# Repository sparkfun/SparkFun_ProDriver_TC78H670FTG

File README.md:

SparkFun ProDriver - Stepper Motor Driver (TC78H670FTG)
========================================

[*SparkFun ProDriver - Stepper Motor Driver (TC78H670FTG) (ROB-16836)*](https://www.sparkfun.com/products/16836)

The SparkFun ProDriver makes it easy to start developing with the TC78H670FTG bipolar stepper motor driver from Toshiba! Latch terminals provide instant solder-less connections to every feature offered. Use our extensive Arduino Library with 10 examples, and you can quickly explore the many features of this precise and small package size motor driver IC.

In addition to high resolution control (down to 1/128th of a step), the ProDriver can be controlled via traditional clock-in stepping or serial commands. Both methods are demonstrated in the Arduino Library. The serial command method is especially unique in that it allows the user to precisely control the phase, torque, current limit and mixed decay ratio of each coil immediately during stepping. Most stepper motor driver ICs require using an external trimpot to set the current limit, but with the ProDriver, you can precisely adjust this via serial commands!

Repository Contents
-------------------

* **/Documentation** - Datasheets, additional product information
* **/Hardware** - Eagle design files (.brd, .sch)
* **/Hardware/Production** - Production panel files and gerbers (.brd)

Documentation
--------------

* **[Hookup Guide](https://learn.sparkfun.com/tutorials/1200)** - A hookup guide for the SparkFun ProDriver and Mini Stepper Motor Driver (TC78H670FTG)
* **[Arduino Library](https://github.com/sparkfun/SparkFun_ProDriver_TC78H670FTG_Arduino_Library)** - Basic Arduino Library for the SparkFun ProDriver and Mini Stepper Motor Driver (TC78H670FTG)

Product Variants
----------------
* SparkFun Mini Stepper Motor Driver - TC78H670FTG
  * [ROB-25167](https://www.sparkfun.com/products/25167)- v1.0, Initial Release
* SparkFun ProDriver - Stepper Motor Driver (TC78H670FTG)
  * [ROB-16836](https://www.sparkfun.com/products/16836)- v1.0, Initial Release

Product Versions
----------------
* [v01](https://github.com/sparkfun/SparkFun_ProDriver_TC78H670FTG/releases/tag/v10) - Initial Release

License Information
-------------------

This product is _**open source**_!

Please review the LICENSE.md file for license information.

If you have any questions or concerns on licensing, please contact technical support on our [SparkFun forums](https://forum.sparkfun.com/viewforum.php?f=152).

Distributed as-is; no warranty is given.

- Your friends at SparkFun.

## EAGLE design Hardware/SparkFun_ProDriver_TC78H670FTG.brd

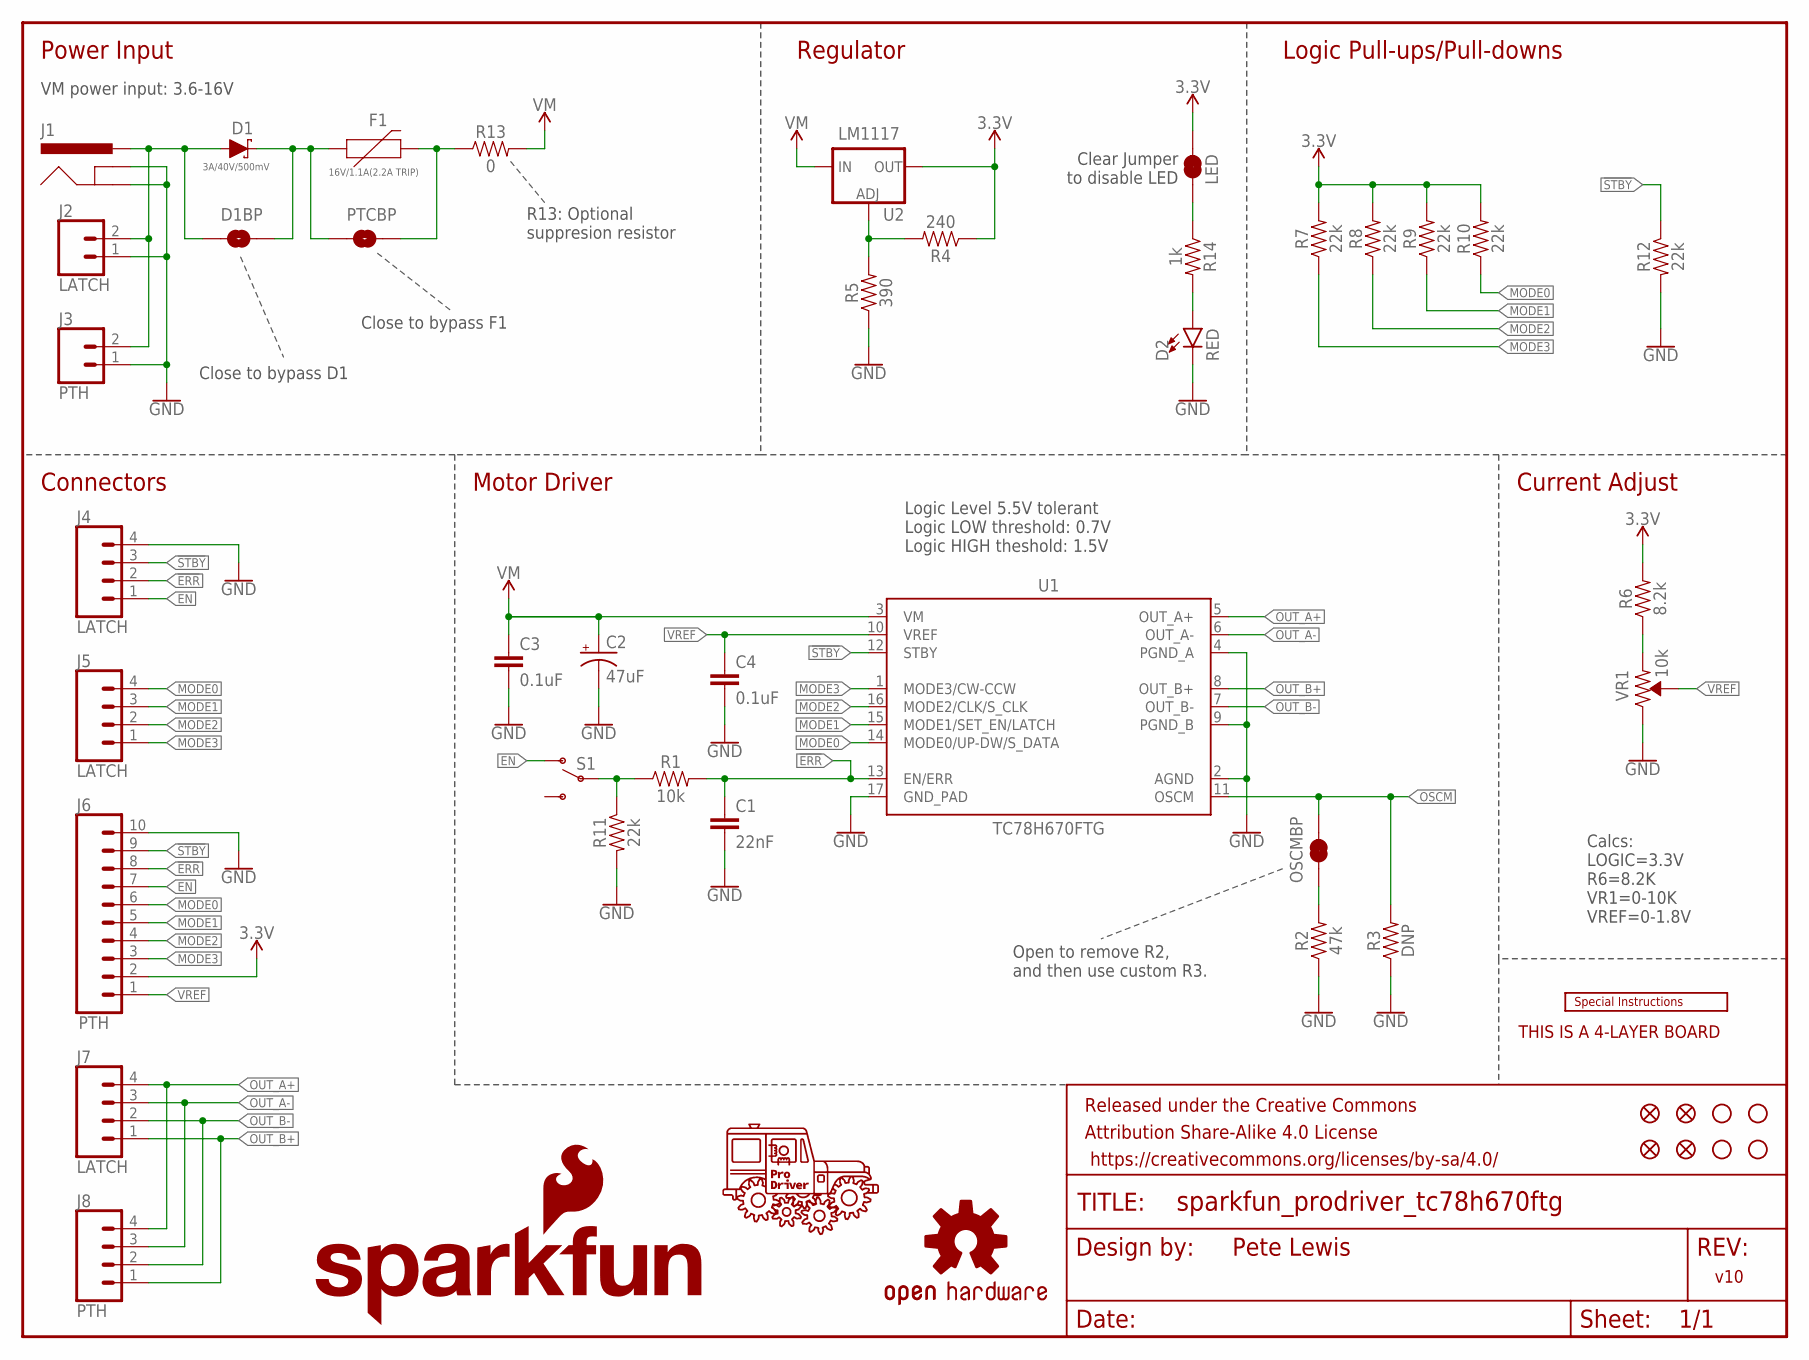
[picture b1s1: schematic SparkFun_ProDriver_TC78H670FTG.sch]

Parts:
C1: 22nF; 0603
C2: 47uF; PANASONIC_D
C3, C4: 0.1uF; 0603
D1: 3A/40V/500mV; SMA-DIODE
D1BP: JUMPER-SMT_2_NO_SILK; SMT-JUMPER_2_NO_SILK
D2: RED; LED-0603
F1: 16V/1.1A(2.2A TRIP); 1210
FID1, FID2, FID3, FID4: FIDUCIAL1X2; FIDUCIAL-1X2
FRAME1: FRAME-LETTER; CREATIVE_COMMONS
J1: POWER_JACKTOE; POWER_JACK_SMD_OVERPASTE_TOE
J2: LATCH; LATCHTERMINAL-5MM-2
J3: PTH; 1X02_NO_SILK
J4, J5, J7: LATCH; LATCHTERMINAL-5MM-4
J6: PTH; 1X10_NO_SILK
J8: PTH; 1X04_NO_SILK
JP4: LED; SMT-JUMPER_2_NC_TRACE_SILK
LOGO1: SFE_LOGO_NAME_FLAME.1_INCH; SFE_LOGO_NAME_FLAME_.1
LOGO2: OSHW-LOGOS; OSHW-LOGO-S
LOGO3: SPECIAL_INSTRUCTIONS-ORDERING; ORDERING_INSTRUCTIONS
OSCMBP: JUMPER-SMT_2_NC_TRACE_SILK; SMT-JUMPER_2_NC_TRACE_SILK
PTCBP: JUMPER-SMT_2_NO_SILK; SMT-JUMPER_2_NO_SILK
R1: 10k; 0603
R2: 47k; 0603
R3: DNP; AXIAL-0.3
R4: 240; 0603
R5: 390; 0603
R6: 8.2k; 0603
R7, R8, R9, R10, R11, R12: 22k; 0603
R13: 0; 0603
R14: 1k; 0603
S1: SWITCH-SPDT-PTH-11.6X4.0MM-LOCK; SWITCH_SPDT_PTH_11.6X4.0MM_LOCK
STANDOFF1, STANDOFF2, STANDOFF3, STANDOFF4: STAND-OFF
U1: TC78H670FTG; P-VQFN16-0303-0.50-001
U2: LM1117; SOT223
U$41: PRODRIVER_LOGO
VR1: 10k; TRIMPOT-SMD-3MM-CLOSED

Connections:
3.3V: J6.2, JP4.2, R4.1, R6.2, R7.2, R8.2, R9.2, R10.2, U2.2 (OUT), U2.4 (OUT)
!ERR: C1.1, J4.2, J6.8, R1.2, U1.13 (EN/ERR)
!STBY: J4.3, J6.9, R12.1, U1.12 (STBY)
EN: J4.1, J6.7, S1.1 (O)
GND: C1.2, C2.-, C3.2, C4.2, D2.C, J1.GND (GNDBREAK), J1.P$4 (GND), J2.1, J3.1, J4.4, J6.10, R2.1, R3.P$1 (1), R5.1, R11.2, R12.2, U1.2 (AGND), U1.4 (PGND_A), U1.9 (PGND_B), U1.17 (GND_PAD), VR1.3 (CW)
MODE0: J5.4, J6.6, R10.1, U1.14 (MODE0/UP-DW/S_DATA)
MODE1: J5.3, J6.5, R9.1, U1.15 (MODE1/SET_EN/LATCH)
MODE2: J5.2, J6.4, R8.1, U1.16 (MODE2/CLK/S_CLK)
MODE3: J5.1, J6.3, R7.1, U1.1 (MODE3/CW-CCW)
unnamed: D1.C, D1BP.2, F1.1, PTCBP.1
unnamed: OSCMBP.1, R2.2
unnamed: F1.2, PTCBP.2, R13.1
unnamed: R4.2, R5.2, U2.1 (ADJ)
unnamed: R6.1, VR1.1 (CCW)
unnamed: D2.A, R14.2
unnamed: R1.1, R11.1, S1.2
unnamed: JP4.1, R14.1
OSCM: OSCMBP.2, R3.P$2 (2), U1.11 (OSCM)
OUT_A+: J7.4, J8.4, U1.5 (OUT_A+)
OUT_A-: J7.3, J8.3, U1.6 (OUT_A-)
OUT_B+: J7.1, J8.1, U1.8 (OUT_B+)
OUT_B-: J7.2, J8.2, U1.7 (OUT_B-)
RAW: D1.A, D1BP.1, J1.VIN0 (PWR), J2.2, J3.2
VM: C2.+, C3.1, R13.2, U1.3 (VM), U2.3 (IN)
VREF: C4.1, J6.1, U1.10 (VREF), VR1.2 (WIPER)

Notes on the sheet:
v10
Pete Lewis
Power Input
Regulator
Logic Pull-ups/Pull-downs
Connectors
Motor Driver
Current Adjust
Open to remove R2, and then use custom R3.
Close to bypass F1
Close to bypass D1
R13: Optional suppresion resistor
Calcs: LOGIC=3.3V R6=8.2K VR1=0-10K VREF=0-1.8V
Clear Jumper to disable LED
VM power input: 3.6-16V
THIS IS A 4-LAYER BOARD
Logic Level 5.5V tolerant Logic LOW threshold: 0.7V Logic HIGH theshold: 1.5V

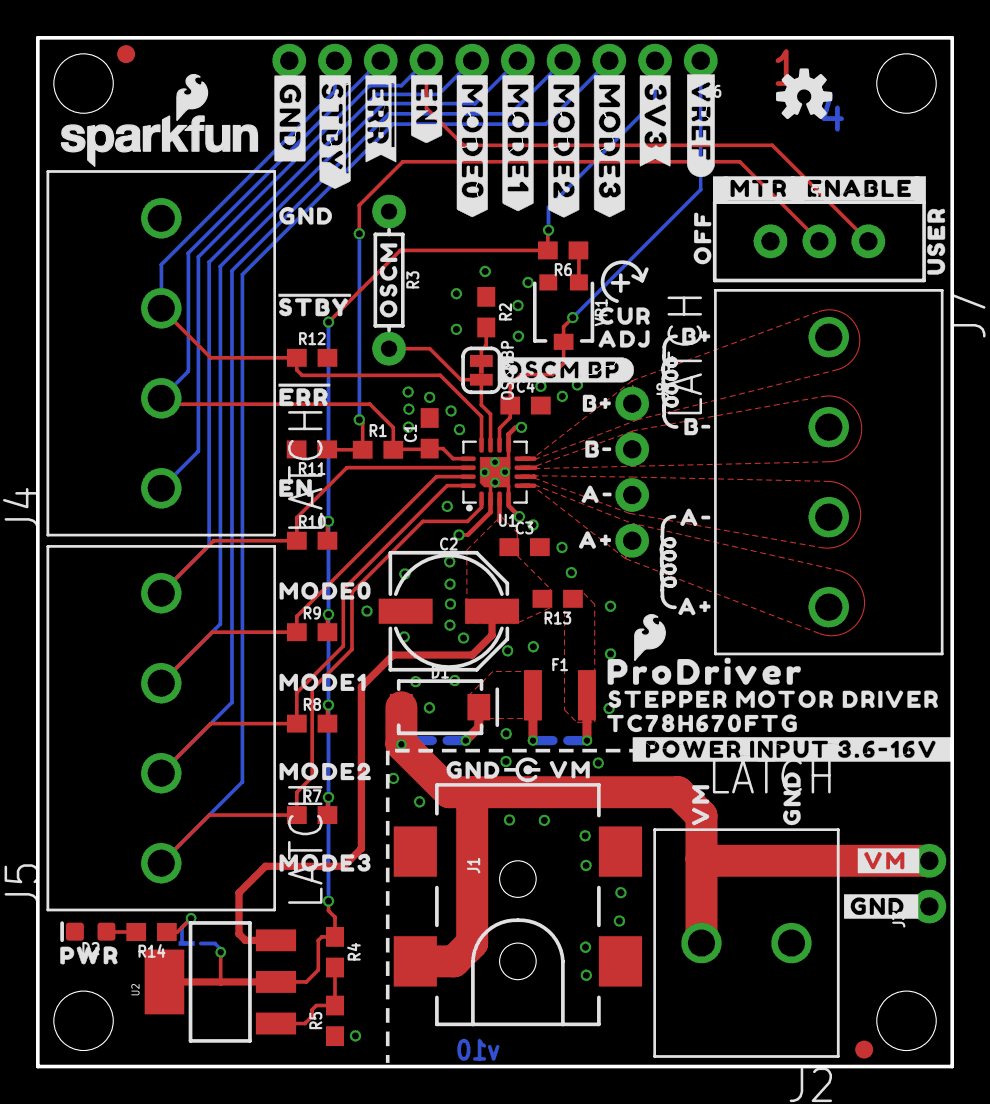
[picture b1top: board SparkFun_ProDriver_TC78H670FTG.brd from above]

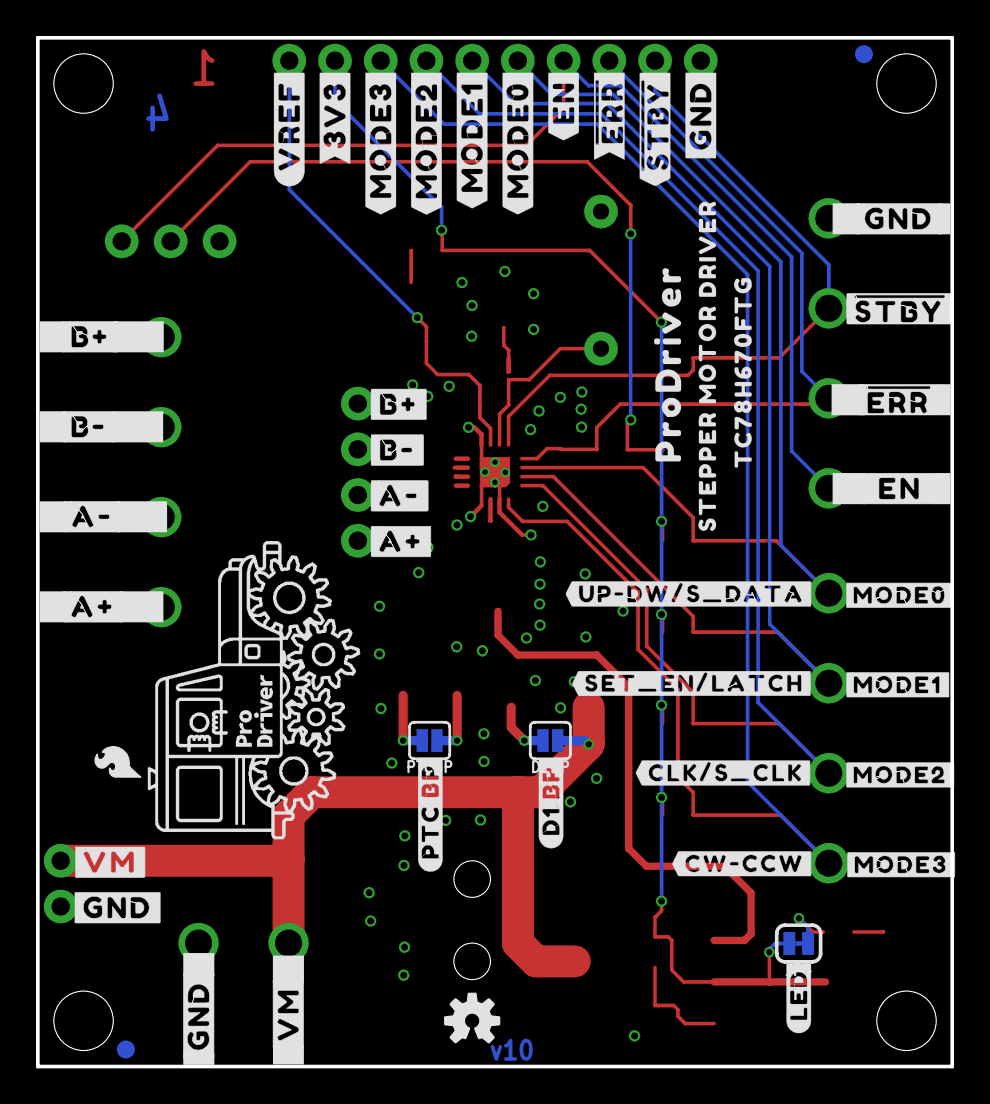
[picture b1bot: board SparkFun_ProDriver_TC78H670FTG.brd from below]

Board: 4 copper layers, 50.8 x 57.1 mm, 139 parts (48 on the bottom side), 25 nets.

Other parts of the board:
LOGO5: SFE_LOGO_NAME_FLAME.1_INCH; SFE_LOGO_FLAME_.1
LOGO6: SFE_LOGO_FLAME.1_INCH; SFE_LOGO_FLAME_.1
U$1, U$44: A#2
U$2, U$42: B#0
U$3, U$15: B#1
U$4, U$43: A#3
U$5, U$12, U$29: GND6
U$6, U$84: TC78H670FTG0
U$7: USER0
U$8: #ERR#3
U$9, U$85: STEPPER_MOTOR_DRIVER0
U$10: CUR0
U$11, U$30: VM10
U$13: #EN#2
U$14: #MTR#0
U$16: #OSCM_BP#0
U$17: OFF0
U$18: OSCM0
U$19: EN0
U$20: ADJ0
U$21: #ENABLE#0
U$22: CURRENT_ADJUST
U$23: MODE30
U$24: MODE10
U$25: MODE20
U$26: MODE00
U$27: #GND_#0
U$28: #VM_#0
U$31, U$69, U$73: #GND#0
U$32: #VREF#0
U$33: #MODE0#4
U$34, U$35: ##ERR##5
U$36: #_POWER_INPUT_3#6#16V_#0
U$37, U$56: #B##0
U$38: #LED#10
U$40, U$86: PRODRIVER0
U$46: #MODE1#4
U$47: #MODE2#4
U$48: #MODE3#4
U$49, U$57: #B##1
U$50, U$58: #A##2
U$51, U$59: #A##3
U$52: #GND#5
U$53: ##STBY##1
U$54: ##STBY##7
U$55: #_EN_#0
U$60: #MODE0#0
U$61: #MODE1#0
U$62: #MODE2#0
U$63: #MODE3#0
U$64: #D1_BP#10
U$65: #CLK#S_CLK#0
U$66: #SET_EN#LATCH#0
U$67: #UP#DW#S_DATA#0
U$68, U$72: #VM#0
U$70: #PTC_BP#9
U$71: OSHW-LOGO-S
U$74: #MODE0#1
U$75, U$93: #3V3#4
U$80: #VREF#4
U$82: #CW#CCW#0
U$83: PWR0
U$87: ##STBY##0
U$89: #STBY#2
U$90: #MODE1#1
U$91: #MODE2#2
U$92: #MODE3#3
U$94: #EN#5
U$95: ##ERR##6
U$96: #GND#8

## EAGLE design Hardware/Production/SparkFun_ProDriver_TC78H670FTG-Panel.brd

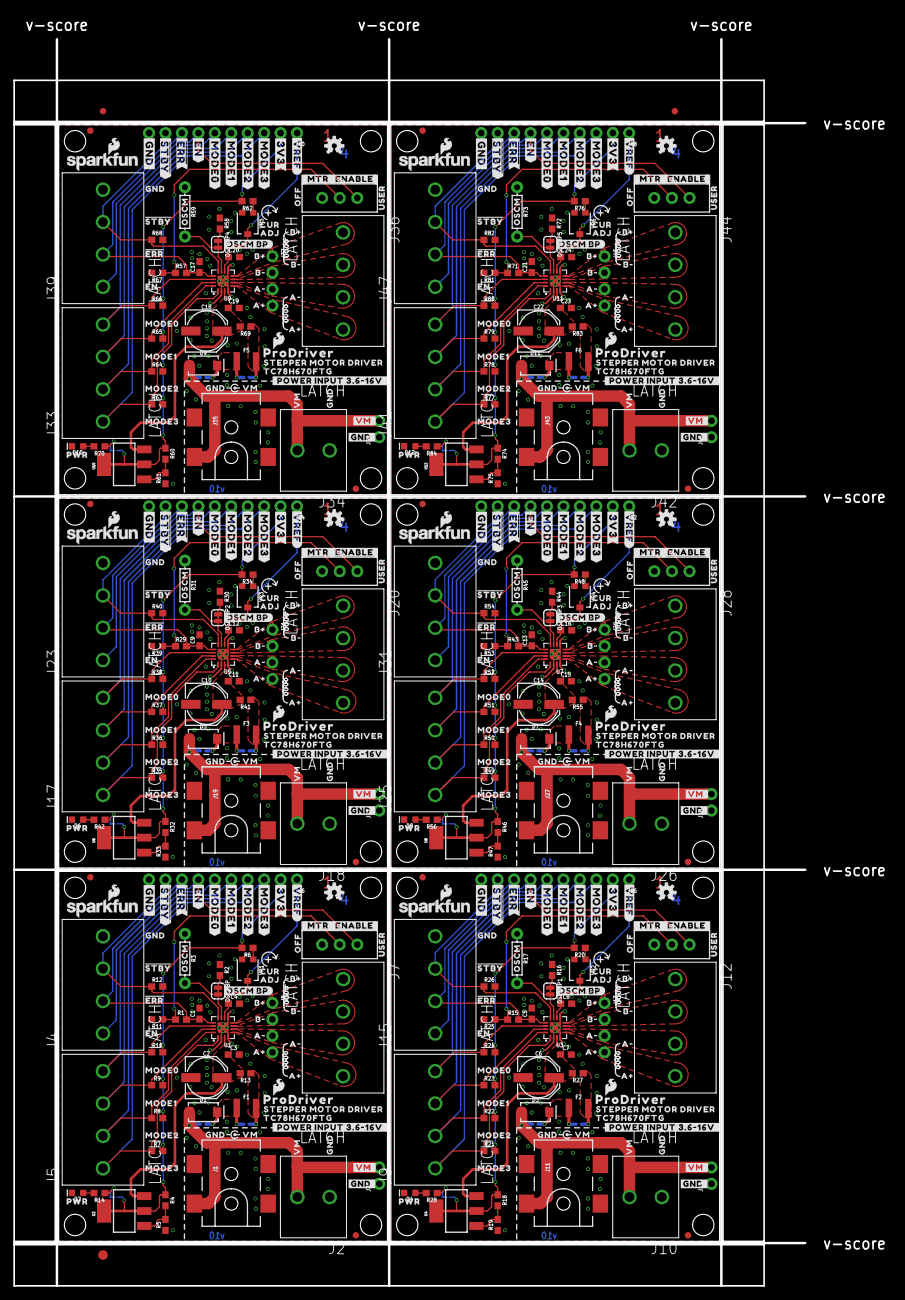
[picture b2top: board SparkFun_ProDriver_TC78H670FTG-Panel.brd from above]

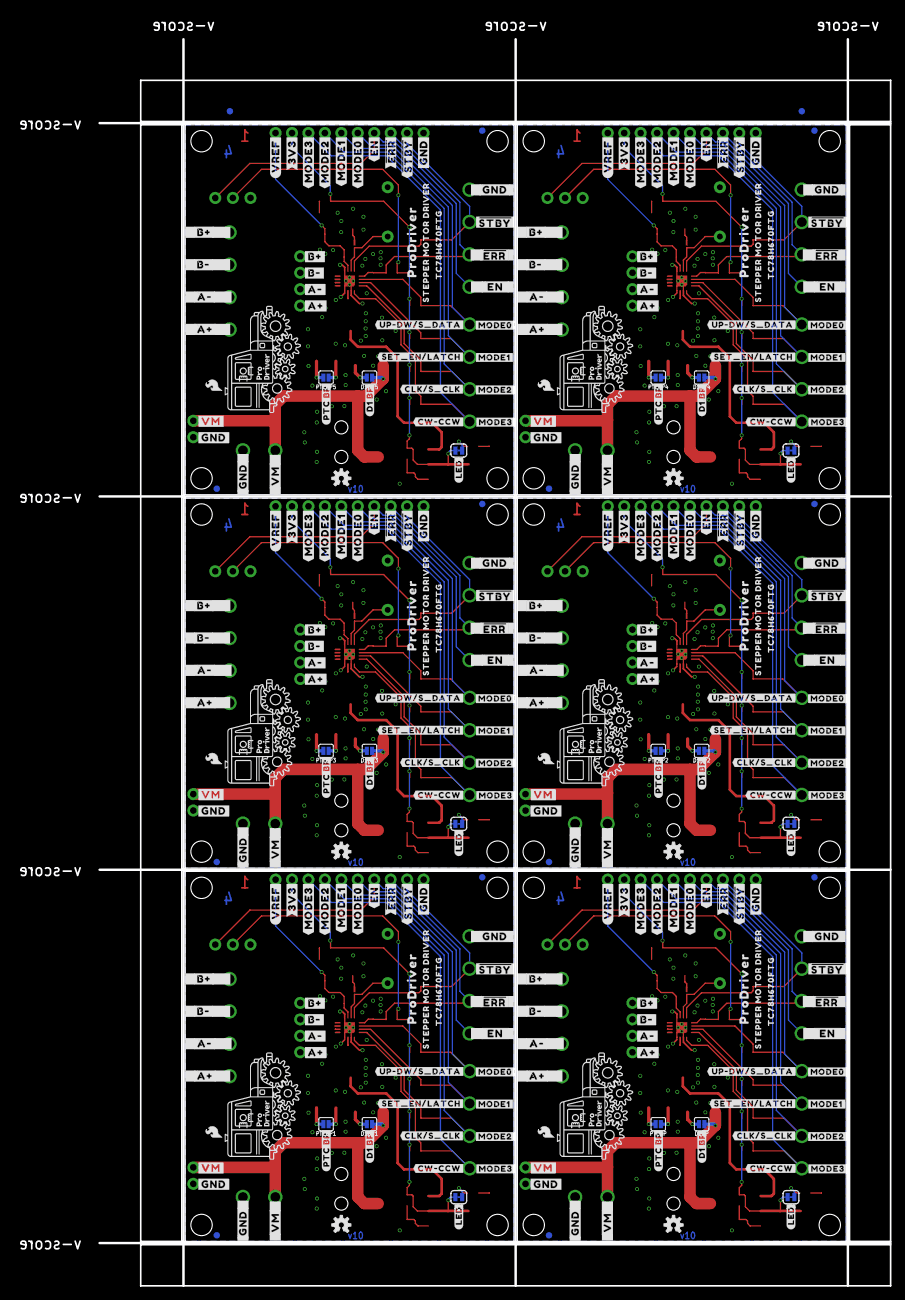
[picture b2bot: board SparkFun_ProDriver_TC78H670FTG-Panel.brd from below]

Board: 4 copper layers, 122.2 x 192.5 mm, 827 parts (290 on the bottom side), 150 nets.

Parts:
C1, C5, C9, C13, C17, C21: 22nF; 0603
C2, C6, C10, C14, C18, C22: 47uF; PANASONIC_D
C3, C4, C7, C8, C11, C12, C15, C16, C19, C20, C23, C24: 0.1uF; 0603
D1, D3, D5, D7, D9, D11: 3A/40V/500mV; SMA-DIODE
D1BP, D1BP1, D1BP2, D1BP3, D1BP4, D1BP5: SMT-JUMPER_2_NO_SILK
D2, D4, D6, D8, D10, D12: RED; LED-0603
E$1, E$2, E$3, E$4: FIDUCIAL-1X2
E$5: FIDUCIAL-1.5X3
F1, F2, F3, F4, F5, F6: 16V/1.1A(2.2A TRIP); 1210
FID1, FID2, FID3, FID4, FID5, FID6, FID7, FID8, FID9, FID10, FID11, FID12, FID13, FID14, FID15, FID16, FID17, FID18, FID19, FID20, FID21, FID22, FID23, FID24: FIDUCIAL1X2; FIDUCIAL-1X2
J1, J11, J19, J27, J35, J43: POWER_JACK_SMD_OVERPASTE_TOE
J2, J10, J18, J26, J34, J42: LATCH; LATCHTERMINAL-5MM-2
J3, J14, J22, J30, J38, J46: PTH; 1X02_NO_SILK
J4, J5, J7, J9, J12, J15, J17, J20, J23, J25, J28, J31, J33, J36, J39, J41, J44, J47: LATCH; LATCHTERMINAL-5MM-4
J6, J16, J24, J32, J40, J48: PTH; 1X10_NO_SILK
J8, J13, J21, J29, J37, J45: PTH; 1X04_NO_SILK
JP1, JP2, JP3, JP4, JP5, JP6: LED; SMT-JUMPER_2_NC_TRACE_SILK
LOGO1, LOGO3, LOGO9, LOGO13, LOGO17, LOGO21: SFE_LOGO_NAME_FLAME.1_INCH; SFE_LOGO_NAME_FLAME_.1
LOGO2, LOGO4, LOGO10, LOGO14, LOGO18, LOGO22: OSHW-LOGOS; OSHW-LOGO-S
LOGO5, LOGO7, LOGO11, LOGO15, LOGO19, LOGO23: SFE_LOGO_NAME_FLAME.1_INCH; SFE_LOGO_FLAME_.1
LOGO6, LOGO8, LOGO12, LOGO16, LOGO20, LOGO24: SFE_LOGO_FLAME.1_INCH; SFE_LOGO_FLAME_.1
OSCMBP, OSCMBP1, OSCMBP2, OSCMBP3, OSCMBP4, OSCMBP5: SMT-JUMPER_2_NC_TRACE_SILK
PTCBP, PTCBP1, PTCBP2, PTCBP3, PTCBP4, PTCBP5: SMT-JUMPER_2_NO_SILK
R1, R15, R29, R43, R57, R71: 10k; 0603
R2, R16, R30, R44, R58, R72: 47k; 0603
R3, R17, R31, R45, R59, R73: DNP; AXIAL-0.3
R4, R18, R32, R46, R60, R74: 240; 0603
R5, R19, R33, R47, R61, R75: 390; 0603
R6, R20, R34, R48, R62, R76: 8.2k; 0603
R7, R8, R9, R10, R11, R12, R21, R22, R23, R24, R25, R26, R35, R36, R37, R38, R39, R40, R49, R50, R51, R52, R53, R54, R63, R64, R65, R66, R67, R68, R77, R78, R79, R80, R81, R82: 22k; 0603
R13, R27, R41, R55, R69, R83: 0; 0603
R14, R28, R42, R56, R70, R84: 1k; 0603
S1, S2, S3, S4, S5, S6: SWITCH_SPDT_PTH_11.6X4.0MM_LOCK
STANDOFF1, STANDOFF2, STANDOFF3, STANDOFF4, STANDOFF5, STANDOFF6, STANDOFF7, STANDOFF8, STANDOFF9, STANDOFF10, STANDOFF11, STANDOFF12, STANDOFF13, STANDOFF14, STANDOFF15, STANDOFF16, STANDOFF17, STANDOFF18, STANDOFF19, STANDOFF20, STANDOFF21, STANDOFF22, STANDOFF23, STANDOFF24: STAND-OFF
U1, U3, U5, U7, U9, U11: TC78H670FTG; P-VQFN16-0303-0.50-001
U2, U4, U6, U8, U10, U12: LM1117; SOT223
U$1, U$44, U$76, U$118, U$179, U$206, U$267, U$294, U$355, U$382, U$443, U$470: A#2
U$2, U$39, U$42, U$116, U$177, U$204, U$265, U$292, U$353, U$380, U$441, U$468: B#0
U$3, U$15, U$45, U$115, U$178, U$203, U$266, U$291, U$354, U$379, U$442, U$467: B#1
U$4, U$43, U$77, U$117, U$180, U$205, U$268, U$293, U$356, U$381, U$444, U$469: A#3
U$5, U$12, U$29, U$78, U$81, U$107, U$181, U$183, U$195, U$269, U$271, U$283, U$357, U$359, U$371, U$445, U$447, U$459: GND6
U$6, U$84, U$109, U$149, U$197, U$237, U$285, U$325, U$373, U$413, U$461, U$501: TC78H670FTG0
U$7, U$157, U$245, U$333, U$421, U$509: USER0
U$8, U$155, U$243, U$331, U$419, U$507: #ERR#3
U$9, U$85, U$110, U$150, U$198, U$238, U$286, U$326, U$374, U$414, U$462, U$502: STEPPER_MOTOR_DRIVER0
U$10, U$98, U$186, U$274, U$362, U$450: CUR0
U$11, U$30, U$79, U$108, U$182, U$196, U$270, U$284, U$358, U$372, U$446, U$460: VM10
U$13, U$120, U$208, U$296, U$384, U$472: #EN#2
U$14, U$113, U$201, U$289, U$377, U$465: #MTR#0
U$16, U$158, U$246, U$334, U$422, U$510: #OSCM_BP#0
U$17, U$88, U$184, U$272, U$360, U$448: OFF0
U$18, U$97, U$185, U$273, U$361, U$449: OSCM0
U$19, U$119, U$207, U$295, U$383, U$471: EN0
U$20, U$99, U$187, U$275, U$363, U$451: ADJ0
U$21, U$114, U$202, U$290, U$378, U$466: #ENABLE#0
U$22, U$100, U$188, U$276, U$364, U$452: CURRENT_ADJUST
U$23, U$101, U$189, U$277, U$365, U$453: MODE30
U$24, U$102, U$190, U$278, U$366, U$454: MODE10
U$25, U$103, U$191, U$279, U$367, U$455: MODE20
U$26, U$104, U$192, U$280, U$368, U$456: MODE00
U$27, U$105, U$193, U$281, U$369, U$457: #GND_#0
U$28, U$106, U$194, U$282, U$370, U$458: #VM_#0
U$31, U$69, U$73, U$111, U$144, U$146, U$199, U$232, U$234, U$287, U$320, U$322, U$375, U$408, U$410, U$463, U$496, U$498: #GND#0
U$32, U$125, U$213, U$301, U$389, U$477: #VREF#0
U$33, U$121, U$209, U$297, U$385, U$473: #MODE0#4
U$34, U$35, U$156, U$175, U$244, U$263, U$332, U$351, U$420, U$439, U$508, U$527: ##ERR##5
U$36, U$176, U$264, U$352, U$440, U$528: #_POWER_INPUT_3#6#16V_#0
U$37, U$56, U$126, U$132, U$214, U$220, U$302, U$308, U$390, U$396, U$478, U$484: #B##0
U$38, U$173, U$261, U$349, U$437, U$525: #LED#10
U$40, U$86, U$112, U$151, U$200, U$239, U$288, U$327, U$376, U$415, U$464, U$503: PRODRIVER0
U$41, U$159, U$247, U$335, U$423, U$511: PRODRIVER_LOGO
U$46, U$122, U$210, U$298, U$386, U$474: #MODE1#4
U$47, U$123, U$211, U$299, U$387, U$475: #MODE2#4
U$48, U$124, U$212, U$300, U$388, U$476: #MODE3#4
U$49, U$57, U$127, U$133, U$215, U$221, U$303, U$309, U$391, U$397, U$479, U$485: #B##1
U$50, U$58, U$128, U$134, U$216, U$222, U$304, U$310, U$392, U$398, U$480, U$486: #A##2
U$51, U$59, U$129, U$135, U$217, U$223, U$305, U$311, U$393, U$399, U$481, U$487: #A##3
U$52, U$130, U$218, U$306, U$394, U$482: #GND#5
U$53, U$153, U$241, U$329, U$417, U$505: ##STBY##1
U$54, U$169, U$257, U$345, U$433, U$521: ##STBY##7
U$55, U$131, U$219, U$307, U$395, U$483: #_EN_#0
U$60, U$136, U$224, U$312, U$400, U$488: #MODE0#0
U$61, U$137, U$225, U$313, U$401, U$489: #MODE1#0
U$62, U$138, U$226, U$314, U$402, U$490: #MODE2#0
U$63, U$139, U$227, U$315, U$403, U$491: #MODE3#0
U$64, U$172, U$260, U$348, U$436, U$524: #D1_BP#10
U$65, U$140, U$228, U$316, U$404, U$492: #CLK#S_CLK#0
U$66, U$141, U$229, U$317, U$405, U$493: #SET_EN#LATCH#0
U$67, U$142, U$230, U$318, U$406, U$494: #UP#DW#S_DATA#0
U$68, U$72, U$143, U$145, U$231, U$233, U$319, U$321, U$407, U$409, U$495, U$497: #VM#0
U$70, U$171, U$259, U$347, U$435, U$523: #PTC_BP#9
U$71, U$160, U$248, U$336, U$424, U$512: OSHW-LOGO-S
U$74, U$161, U$249, U$337, U$425, U$513: #MODE0#1
U$75, U$93, U$165, U$174, U$253, U$262, U$341, U$350, U$429, U$438, U$517, U$526: #3V3#4
U$80, U$166, U$254, U$342, U$430, U$518: #VREF#4
U$82, U$147, U$235, U$323, U$411, U$499: #CW#CCW#0
U$83, U$148, U$236, U$324, U$412, U$500: PWR0
U$87, U$152, U$240, U$328, U$416, U$504: ##STBY##0
U$89, U$154, U$242, U$330, U$418, U$506: #STBY#2
U$90, U$162, U$250, U$338, U$426, U$514: #MODE1#1
U$91, U$163, U$251, U$339, U$427, U$515: #MODE2#2
U$92, U$164, U$252, U$340, U$428, U$516: #MODE3#3
U$94, U$167, U$255, U$343, U$431, U$519: #EN#5
U$95, U$168, U$256, U$344, U$432, U$520: ##ERR##6
U$96, U$170, U$258, U$346, U$434, U$522: #GND#8
VR1, VR2, VR3, VR4, VR5, VR6: 10k; TRIMPOT-SMD-3MM-CLOSED

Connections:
3.3V: J6.2, JP4.2, R4.1, R6.2, R7.2, R8.2, R9.2, R10.2, U2.2, U2.4
3.3V1: J16.2, JP1.2, R18.1, R20.2, R21.2, R22.2, R23.2, R24.2, U4.2, U4.4
3.3V2: J24.2, JP2.2, R32.1, R34.2, R35.2, R36.2, R37.2, R38.2, U6.2, U6.4
3.3V3: J32.2, JP3.2, R46.1, R48.2, R49.2, R50.2, R51.2, R52.2, U8.2, U8.4
3.3V4: J40.2, JP5.2, R60.1, R62.2, R63.2, R64.2, R65.2, R66.2, U10.2, U10.4
3.3V5: J48.2, JP6.2, R74.1, R76.2, R77.2, R78.2, R79.2, R80.2, U12.2, U12.4
!ERR: C1.1, J4.2, J6.8, R1.2, U1.13
!ERR1: C5.1, J15.2, J16.8, R15.2, U3.13
!ERR2: C9.1, J23.2, J24.8, R29.2, U5.13
!ERR3: C13.1, J31.2, J32.8, R43.2, U7.13
!ERR4: C17.1, J39.2, J40.8, R57.2, U9.13
!ERR5: C21.1, J47.2, J48.8, R71.2, U11.13
!STBY: J4.3, J6.9, R12.1, U1.12
!STBY1: J15.3, J16.9, R26.1, U3.12
!STBY2: J23.3, J24.9, R40.1, U5.12
!STBY3: J31.3, J32.9, R54.1, U7.12
!STBY4: J39.3, J40.9, R68.1, U9.12
!STBY5: J47.3, J48.9, R82.1, U11.12
EN: J4.1, J6.7, S1.1
EN1: J15.1, J16.7, S2.1
EN2: J23.1, J24.7, S3.1
EN3: J31.1, J32.7, S4.1
EN4: J39.1, J40.7, S5.1
EN5: J47.1, J48.7, S6.1
GND: C1.2, C2.-, C3.2, C4.2, D2.C, J1.GND, J1.P$4, J2.1, J3.1, J4.4, J6.10, R2.1, R3.P$1, R5.1, R11.2, R12.2, U1.2, U1.4, U1.9, U1.17, VR1.3
GND1: C5.2, C6.-, C7.2, C8.2, D4.C, J10.1, J11.GND, J11.P$4, J14.1, J15.4, J16.10, R16.1, R17.P$1, R19.1, R25.2, R26.2, U3.2, U3.4, U3.9, U3.17, VR2.3
GND2: C9.2, C10.-, C11.2, C12.2, D6.C, J18.1, J19.GND, J19.P$4, J22.1, J23.4, J24.10, R30.1, R31.P$1, R33.1, R39.2, R40.2, U5.2, U5.4, U5.9, U5.17, VR3.3
GND3: C13.2, C14.-, C15.2, C16.2, D8.C, J26.1, J27.GND, J27.P$4, J30.1, J31.4, J32.10, R44.1, R45.P$1, R47.1, R53.2, R54.2, U7.2, U7.4, U7.9, U7.17, VR4.3
GND4: C17.2, C18.-, C19.2, C20.2, D10.C, J34.1, J35.GND, J35.P$4, J38.1, J39.4, J40.10, R58.1, R59.P$1, R61.1, R67.2, R68.2, U9.2, U9.4, U9.9, U9.17, VR5.3
GND5: C21.2, C22.-, C23.2, C24.2, D12.C, J42.1, J43.GND, J43.P$4, J46.1, J47.4, J48.10, R72.1, R73.P$1, R75.1, R81.2, R82.2, U11.2, U11.4, U11.9, U11.17, VR6.3
MODE0: J5.4, J6.6, R10.1, U1.14
MODE1: J5.3, J6.5, R9.1, U1.15
MODE2: J5.2, J6.4, R8.1, U1.16
MODE3: J5.1, J6.3, R7.1, U1.1
MODE4: J9.1, J16.3, R21.1, U3.1
MODE5: J9.2, J16.4, R22.1, U3.16
MODE6: J9.3, J16.5, R23.1, U3.15
MODE7: J9.4, J16.6, R24.1, U3.14
MODE8: J17.1, J24.3, R35.1, U5.1
MODE9: J17.2, J24.4, R36.1, U5.16
MODE10: J17.3, J24.5, R37.1, U5.15
MODE11: J17.4, J24.6, R38.1, U5.14
MODE12: J25.1, J32.3, R49.1, U7.1
MODE13: J25.2, J32.4, R50.1, U7.16
MODE14: J25.3, J32.5, R51.1, U7.15
MODE15: J25.4, J32.6, R52.1, U7.14
MODE16: J33.1, J40.3, R63.1, U9.1
MODE17: J33.2, J40.4, R64.1, U9.16
MODE18: J33.3, J40.5, R65.1, U9.15
MODE19: J33.4, J40.6, R66.1, U9.14
MODE20: J41.1, J48.3, R77.1, U11.1
MODE21: J41.2, J48.4, R78.1, U11.16
MODE22: J41.3, J48.5, R79.1, U11.15
MODE23: J41.4, J48.6, R80.1, U11.14
unnamed: D1.C, D1BP.2, F1.1, PTCBP.1
unnamed: OSCMBP.1, R2.2
unnamed: F1.2, PTCBP.2, R13.1
unnamed: R4.2, R5.2, U2.1
unnamed: R6.1, VR1.1
unnamed: D2.A, R14.2
unnamed: R1.1, R11.1, S1.2
unnamed: JP4.1, R14.1
unnamed: OSCMBP1.1, R16.2
unnamed: R18.2, R19.2, U4.1
unnamed: R20.1, VR2.1
unnamed: D1BP1.2, D3.C, F2.1, PTCBP1.1
unnamed: F2.2, PTCBP1.2, R27.1
unnamed: D4.A, R28.2
unnamed: JP1.1, R28.1
unnamed: R15.1, R25.1, S2.2
unnamed: OSCMBP2.1, R30.2
unnamed: R32.2, R33.2, U6.1
unnamed: R34.1, VR3.1
unnamed: D1BP2.2, D5.C, F3.1, PTCBP2.1
unnamed: F3.2, PTCBP2.2, R41.1
unnamed: D6.A, R42.2
unnamed: JP2.1, R42.1
unnamed: R29.1, R39.1, S3.2
unnamed: OSCMBP3.1, R44.2
unnamed: R46.2, R47.2, U8.1
unnamed: R48.1, VR4.1
unnamed: D1BP3.2, D7.C, F4.1, PTCBP3.1
unnamed: F4.2, PTCBP3.2, R55.1
unnamed: D8.A, R56.2
unnamed: JP3.1, R56.1
unnamed: R43.1, R53.1, S4.2
unnamed: OSCMBP4.1, R58.2
unnamed: R60.2, R61.2, U10.1
unnamed: R62.1, VR5.1
unnamed: D1BP4.2, D9.C, F5.1, PTCBP4.1
unnamed: F5.2, PTCBP4.2, R69.1
unnamed: D10.A, R70.2
unnamed: JP5.1, R70.1
unnamed: R57.1, R67.1, S5.2
unnamed: OSCMBP5.1, R72.2
unnamed: R74.2, R75.2, U12.1
unnamed: R76.1, VR6.1
unnamed: D1BP5.2, D11.C, F6.1, PTCBP5.1
unnamed: F6.2, PTCBP5.2, R83.1
unnamed: D12.A, R84.2
unnamed: JP6.1, R84.1
unnamed: R71.1, R81.1, S6.2
OSCM: OSCMBP.2, R3.P$2, U1.11
OSCM1: OSCMBP1.2, R17.P$2, U3.11
OSCM2: OSCMBP2.2, R31.P$2, U5.11
OSCM3: OSCMBP3.2, R45.P$2, U7.11
OSCM4: OSCMBP4.2, R59.P$2, U9.11
OSCM5: OSCMBP5.2, R73.P$2, U11.11
OUT_A+: J7.4, J8.4, U1.5
OUT_A+1: J12.4, J13.4, U3.5
OUT_A+2: J20.4, J21.4, U5.5
OUT_A+3: J28.4, J29.4, U7.5
OUT_A+4: J36.4, J37.4, U9.5
OUT_A+5: J44.4, J45.4, U11.5
OUT_A-: J7.3, J8.3, U1.6
OUT_A-1: J12.3, J13.3, U3.6
OUT_A-2: J20.3, J21.3, U5.6
OUT_A-3: J28.3, J29.3, U7.6
OUT_A-4: J36.3, J37.3, U9.6
OUT_A-5: J44.3, J45.3, U11.6
OUT_B+: J7.1, J8.1, U1.8
OUT_B+1: J12.1, J13.1, U3.8
OUT_B+2: J20.1, J21.1, U5.8
OUT_B+3: J28.1, J29.1, U7.8
OUT_B+4: J36.1, J37.1, U9.8
OUT_B+5: J44.1, J45.1, U11.8
OUT_B-: J7.2, J8.2, U1.7
OUT_B-1: J12.2, J13.2, U3.7
OUT_B-2: J20.2, J21.2, U5.7
OUT_B-3: J28.2, J29.2, U7.7
OUT_B-4: J36.2, J37.2, U9.7
OUT_B-5: J44.2, J45.2, U11.7
RAW: D1.A, D1BP.1, J1.VIN0, J2.2, J3.2
RAW1: D1BP1.1, D3.A, J10.2, J11.VIN0, J14.2
RAW2: D1BP2.1, D5.A, J18.2, J19.VIN0, J22.2
RAW3: D1BP3.1, D7.A, J26.2, J27.VIN0, J30.2
RAW4: D1BP4.1, D9.A, J34.2, J35.VIN0, J38.2
RAW5: D1BP5.1, D11.A, J42.2, J43.VIN0, J46.2
VM: C2.+, C3.1, R13.2, U1.3, U2.3
VM1: C6.+, C7.1, R27.2, U3.3, U4.3
VM2: C10.+, C11.1, R41.2, U5.3, U6.3
VM3: C14.+, C15.1, R55.2, U7.3, U8.3
VM4: C18.+, C19.1, R69.2, U9.3, U10.3
VM5: C22.+, C23.1, R83.2, U11.3, U12.3
VREF: C4.1, J6.1, U1.10, VR1.2
VREF1: C8.1, J16.1, U3.10, VR2.2
VREF2: C12.1, J24.1, U5.10, VR3.2
VREF3: C16.1, J32.1, U7.10, VR4.2
VREF4: C20.1, J40.1, U9.10, VR5.2
VREF5: C24.1, J48.1, U11.10, VR6.2

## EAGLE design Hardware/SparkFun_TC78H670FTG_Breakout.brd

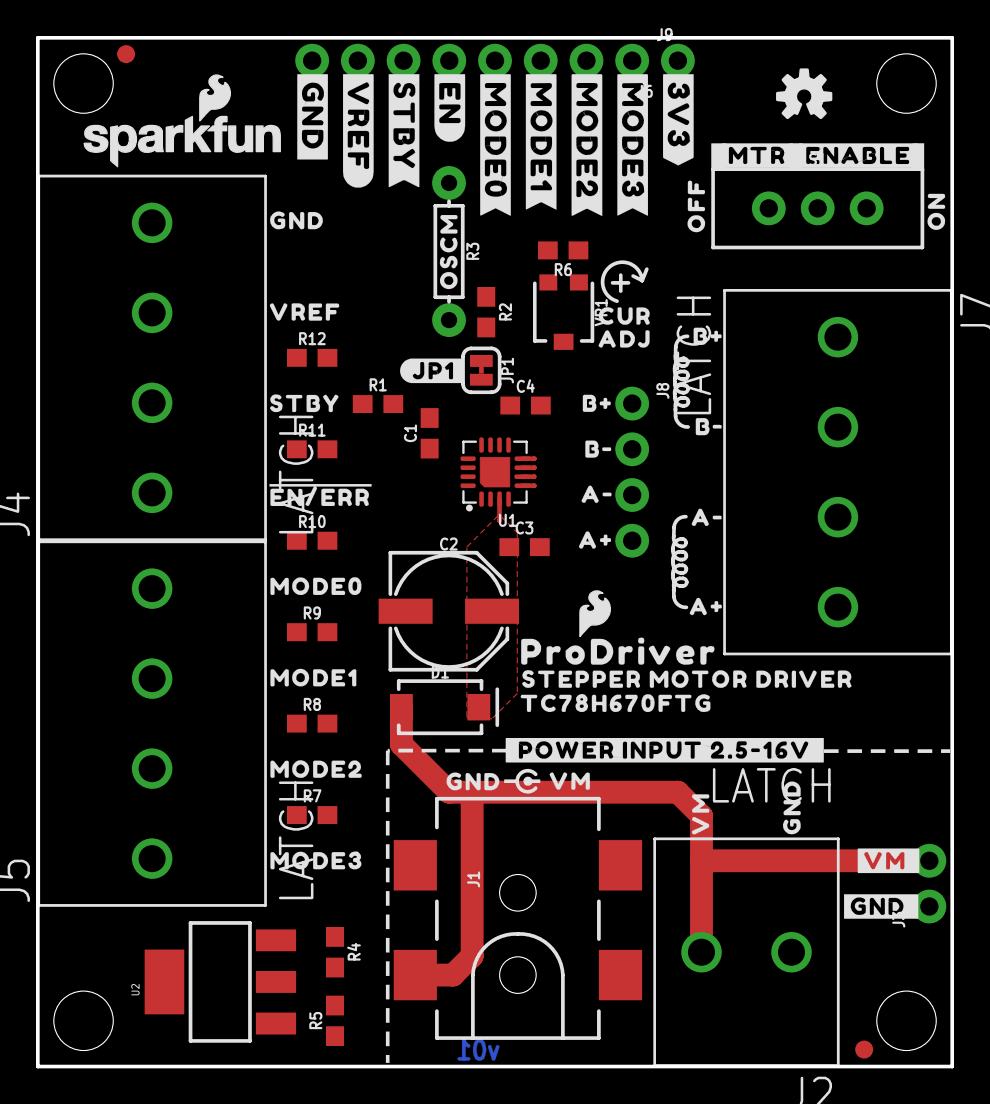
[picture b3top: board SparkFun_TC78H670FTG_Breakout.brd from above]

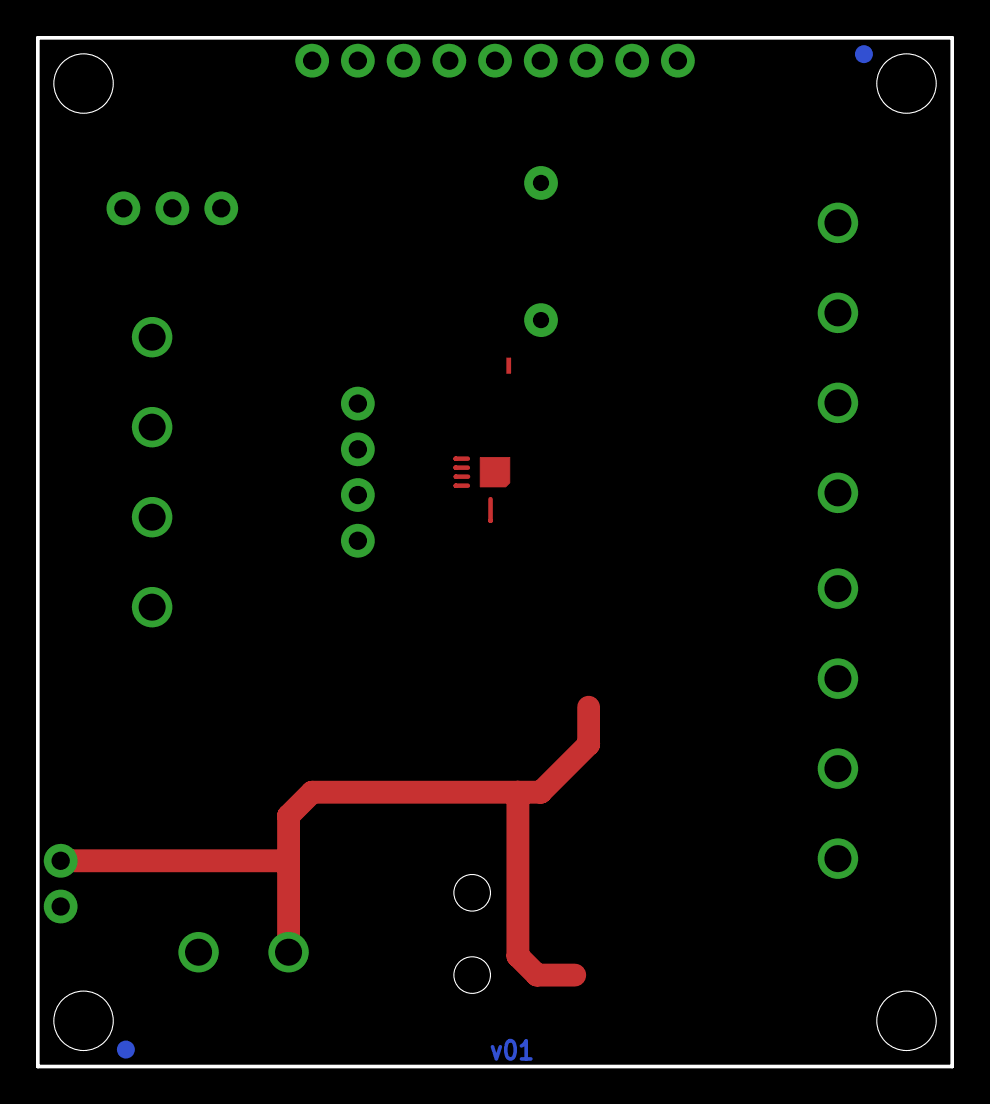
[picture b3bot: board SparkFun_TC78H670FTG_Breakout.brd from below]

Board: 4 copper layers, 50.8 x 57.1 mm, 87 parts (2 on the bottom side), 20 nets.

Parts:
C1: 22nF; 0603
C2: 47uF; PANASONIC_D
C3, C4: 0.1uF; 0603
D1: 3A/40V/500mV; SMA-DIODE
FID1, FID2, FID3, FID4: FIDUCIAL1X2; FIDUCIAL-1X2
FRAME1: FRAME-LETTER; CREATIVE_COMMONS
J1: POWER_JACK_SMD_OVERPASTE_TOE
J2: LATCH; LATCHTERMINAL-5MM-2
J3: PTH; 1X02_NO_SILK
J4, J5, J7: LATCH; LATCHTERMINAL-5MM-4
J6: PTH; 1X08_NO_SILK
J8: PTH; 1X04_NO_SILK
J9: 1X01_NO_SILK
JP1: SMT-JUMPER_2_NC_TRACE_SILK
LOGO1: SFE_LOGO_NAME_FLAME.1_INCH; SFE_LOGO_NAME_FLAME_.1
LOGO2: OSHW-LOGOS; OSHW-LOGO-S
LOGO4: SFE_LOGO_FLAME.1_INCH; SFE_LOGO_FLAME_.1
R1: 10k; 0603
R2: 47k; 0603
R3: DNP; AXIAL-0.3
R4: 240; 0603
R5: 390; 0603
R6: 8.2k; 0603
R7, R8, R9, R10, R11, R12: 22k; 0603
S1: SWITCH_SPDT_PTH_11.6X4.0MM_LOCK
STANDOFF1, STANDOFF2, STANDOFF3, STANDOFF4: STAND-OFF
U1: TC78H670FTG; P-VQFN16-0303-0.50-001
U2: SOT223
U$1, U$44: A#2
U$2, U$42: B#0
U$3, U$15: B#1
U$4, U$43: A#3
U$5, U$12, U$29: GND6
U$6: TC78H670FTG0
U$7: VREF7
U$8: STBY8
U$9: STEPPER_MOTOR_DRIVER0
U$10: CUR0
U$11, U$30: VM10
U$13: #JP1#0
U$14: #MTR#0
U$16: ON0
U$17: OFF0
U$18: OSCM0
U$19: #EN#ERR#0
U$20: ADJ0
U$21: #ENABLE#0
U$22: CURRENT_ADJUST
U$23: MODE30
U$24: MODE10
U$25: MODE20
U$26: MODE00
U$27: #GND_#0
U$28: #VM_#0
U$31: #GND#0
U$32: #VREF#0
U$33: #STBY#0
U$34: #EN#0
U$35: #MODE0#0
U$36: #MODE1#0
U$37: #MODE2#0
U$38: #MODE3#0
U$39: #3V3#0
U$40: PRODRIVER0
U$41: #_POWER_INPUT_2#5#16V_#0
VR1: 10k; TRIMPOT-SMD-3MM-CLOSED

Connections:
3.3V: J9.1, R4.1, R6.2, R7.2, R8.2, R9.2, R10.2, R11.2, R12.2, U2.2, U2.4
EN: J4.1, J6.5, R1.1, R11.1, S1.2
GND: C1.2, C2.-, C3.2, C4.2, J1.GND, J1.P$4, J2.1, J3.1, J4.4, J6.8, R2.1, R3.P$1, R5.1, S1.3, U1.2, U1.4, U1.9, U1.17, VR1.3
MODE0: J5.4, J6.4, R10.1, U1.14
MODE1: J5.3, J6.3, R9.1, U1.15
MODE2: J5.2, J6.2, R8.1, U1.16
MODE3: J5.1, J6.1, R7.1, U1.1
unnamed: C1.1, R1.2, U1.13
unnamed: JP1.1, R2.2
unnamed: D1.A, J1.VIN0, J2.2, J3.2
unnamed: R4.2, R5.2, U2.1
unnamed: R6.1, VR1.1
OSCM: JP1.2, R3.P$2, U1.11
OUT_A+: J7.4, J8.4, U1.5
OUT_A-: J7.3, J8.3, U1.6
OUT_B+: J7.1, J8.1, U1.8
OUT_B-: J7.2, J8.2, U1.7
STBY: J4.2, J6.6, R12.1, U1.12
VM: C2.+, C3.1, D1.C, U1.3, U2.3
VREF: C4.1, J4.3, J6.7, U1.10, VR1.2

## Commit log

2020-06-15 layout coming along start to lay traces
    polygon crashed eagle, so i figured i better start commiting
2020-06-15 update file name to correct product name
2020-06-15 update name in readme
2020-06-15 layout almost done still need to add bstop for heatsink
2020-06-15 nudged OSCM res away, added bstop for heatsink
2020-06-16 Corrected EN/ERR pin access
2020-06-16 small sch nudge cleanup
2020-06-17 nudged 1x4 latch terminals apart to avoid part collision
2020-06-17 moved connectors inward to allow for depanel blade space
    Also added tcream to IC package
2020-06-17 Added PTC and 0Ohm res to power input
    plus bypass jumpers down below
2020-06-17 added value to lm1117 so it's visible in sch
2020-06-17 bplace labels done
2020-06-17 preivew jpgs for proto review
2020-06-18 rotated GND/VM bottom labels to read same direction as others
2020-06-18 first run of checklist catches (pre-design review)
    -4-layer board warnings in sch, brd, plus 1,2,3,4 in coppers
    -added power LED
    -added specail ordering instructions for 4-layer and 2 oz copper
    -added measures
    -ERR and STBY labels show active low overline now
2020-06-19 ERR and STBY NET names to active low - now with overline
2020-06-19 Moved to pull-downs on EN and STBY
    Because the powerup sequence requires that EN and STBY be low (while VM comes up), we should default these to low. Then the user can wire up these lines to their micro and write them HIGH when necess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
    -Adjusted how the enable hardware slide switch works. Now it simply disconnects the "user" control, so that it lets the pull-down resistor take effect. In this way, it will overide any logic level th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
    -Changes enable switch silk label to "user" indicating that the user must now provide logic control on the latch terminals or PTH headers.
    -Added note in schematic about logic level tolerances
    -re routed and moves some traces to mainta
2020-06-19 Suggestions from design review
    -Jumper names same in sch and brd labels
    -JP1 to OSCM
    -ERR net position aligned with others
    -changed power input silk to 3.3V-16V, also updated sch
    -added more vias near IC, head sink exposed copper, and VM input traces to help heat transfer to inner layers.
2020-06-22 Double-check fixes
    -Eagle Library had storefront SKUs for latch terminals. Corrected to prod IDs.
    -removed unnecessary flame symbol in sch (lcopied a second footprint to keep in board).
    -text font to vector on one sch paragraph
2020-06-22 added dummy traces to 2/15, removed bottom paste on IC package
    -Added some dummy traces to 2/15 inner layers so the CAMmer tool will pick up on them and create gerbers.
    -There was some bottom paste on the IC footprint I never noticed till reviewing gerbers, I think this was left over from the QFN footprint I started from.
    -Also updated preview jpgs to reflect most recent design.
2020-06-22 production files - also decided to go with 1 OZ copper
    -panelized for proto panel order 2x2
    -removed "2OZ Copper" note from special ordering instructions. Fab house for protos (JLC) has huge price jump for 2 OZ, so gonna try 1 OZ for protos and see how heat sinking does.
    -adjusted ordering instrutions text file to reflext black soldermask
2020-07-08 Added new jeep pro driver logo to bottom silk
2020-07-17 Rotated bottom silk labels to match product name/logo
    also updated version number to v10 in brd bottom copper and sch
2020-07-20 Post design reveiew (REDs)
    -Moved R3 (OSCM) away from exposed bottom copper (for the optional heat sink). This is nice to add a little extra clarance in case you want to use a larger heatsink.
2020-07-21 Corrected input voltage range to 3.6-16V on sch and brd
2020-07-22 Production files for v10
2020-08-20 Added SCH PDF and dimensionals (in both PDF and PNG)
2020-08-21 Update SparkFun_ProDriver_TC78H670FTG.brd
    Added dimensions for the latch pin component widths and the enable switch location on the measurements layer
2020-08-31 image, description, links updated in readme
2020-09-04 Update README.md
    Update hookup guide url
2020-09-04 Update README.md
    re-re-fixing the url... back to commit: e8aa293546ec1a456eb855cc0e5e233b9dba66a2
2020-09-15 Replaced IC device to use sparkfun eagle library
2024-04-17 Update LICENSE.md
    Remove carriage returns
    Fix grammar
2024-04-17 Updates for the Mini Stepper Motor Driver
2024-04-17 Update CONTRIBUTING.md
    Fix repo link

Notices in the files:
parts and their libraries:
SparkFun-Aesthetics: Licensing: CC v3.0 Share-Alike You are welcome to use this library for commercial purposes.
SparkFun-Connectors: Licensing: Creative Commons ShareAlike 4.0 International - https://creativecommons.org/licenses/by-sa/4.0
SparkFun-Aesthetics: Released under the Creative Commons
